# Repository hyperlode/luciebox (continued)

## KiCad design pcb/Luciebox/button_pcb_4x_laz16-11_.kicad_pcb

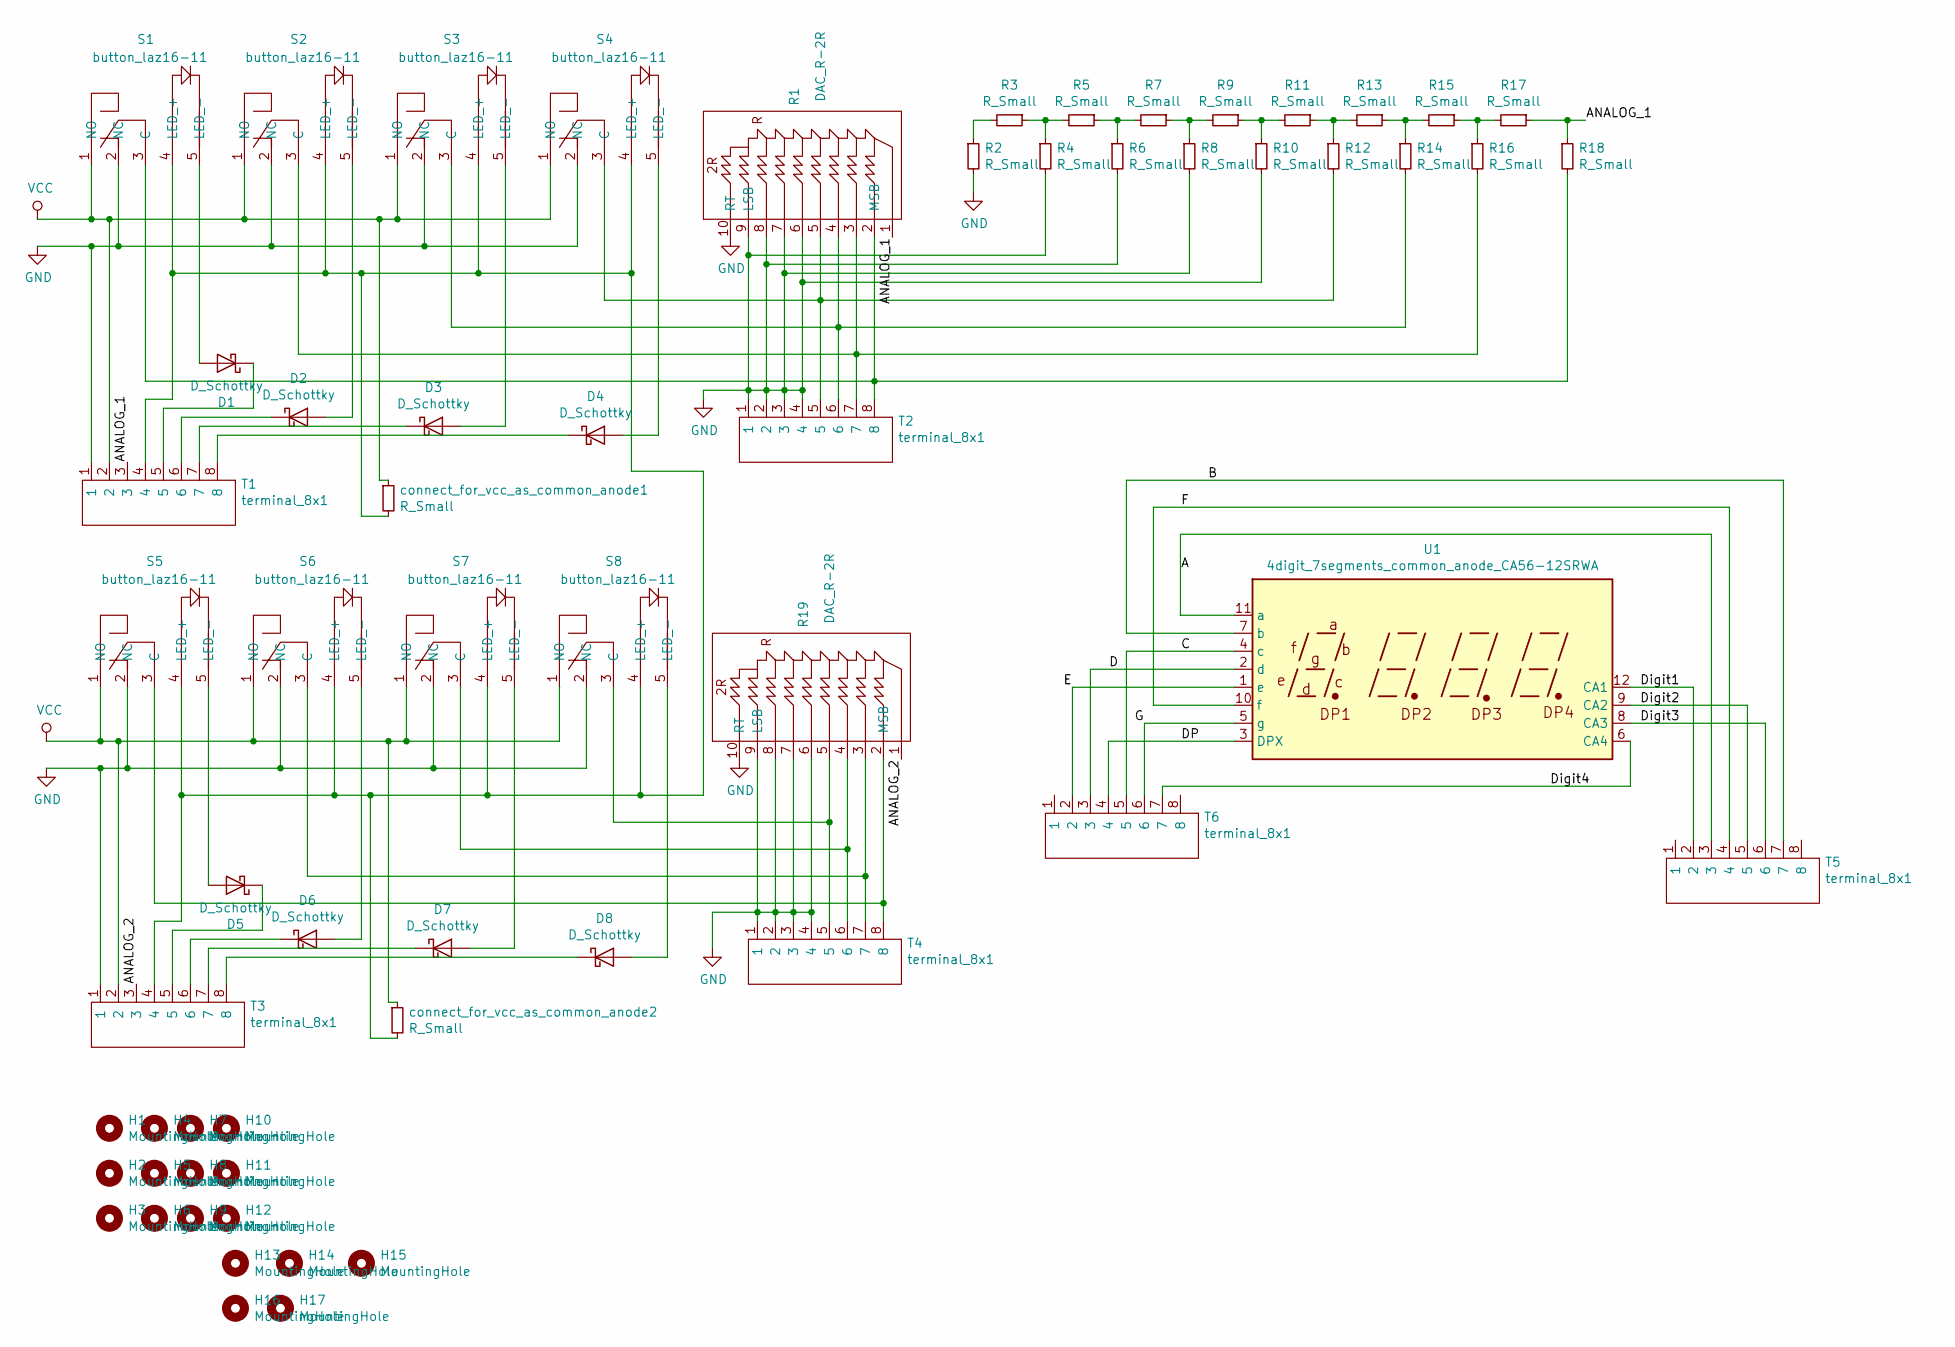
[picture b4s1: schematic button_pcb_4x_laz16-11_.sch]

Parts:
D1, D2, D3, D4, D5, D6, D7, D8: D_Schottky; smd_throughhole_2_pins
H1, H2, H3, H4, H5, H6, H7, H8, H9, H10, H11, H12, H13, H14, H15, H16, H17: MountingHole; MountingHole_4.3mm_M4
R1, R19: DAC_R-2R; SIP-10
R2, R3, R4, R5, R6, R7, R8, R9, R10, R11, R12, R13, R14, R15, R16, R17, R18: R_Small; 1206_0805
S1, S2, S3, S4, S5, S6, S7, S8: button_laz16-11; button_LAZ16-11
T1, T2, T3, T4, T5, T6: terminal_8x1; Terminal_8x1_100mil
U1: 4digit_7segments_common_anode_CA56-12SRWA; CA56-12SRWA
connect_for_vcc_as_common_anode1, connect_for_vcc_as_common_anode2: R_Small; 1206_0805

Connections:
/A: T5.3, U1.11 (a)
/ANALOG_1: R1.1, R17.1, R18.1, T1.3
/ANALOG_2: R19.1, T3.3
/B: T5.7, U1.7 (b)
/C: T6.5, U1.4 (c)
/D: T6.3, U1.2 (d)
/DP: T6.4, U1.3 (DPX)
/Digit1: T5.2, U1.12 (CA1)
/Digit2: T5.5, U1.9 (CA2)
/Digit3: T5.6, U1.8 (CA3)
/Digit4: T6.7, U1.6 (CA4)
/E: T6.2, U1.1 (e)
/F: T5.4, U1.10 (f)
/G: T6.6, U1.5 (g)
GND: R1.6, R1.7, R1.8, R1.9 (LSB), R1.10 (RT), R2.2, R4.2, R6.2, R8.2, R10.2, R19.6, R19.7, R19.8, R19.9 (LSB), R19.10 (RT), S1.2 (NC), S2.2 (NC), S3.2 (NC), S4.2 (NC), S5.2 (NC), S6.2 (NC), S7.2 (NC), S8.2 (NC), T1.1, T2.1, T2.2, T2.3, T2.4, T3.1, T4.1, T4.2, T4.3, T4.4
unnamed: D1.1 (K), T1.5
unnamed: D1.2 (A), S1.5 (LED_-)
unnamed: D2.1 (K), T1.6
unnamed: D2.2 (A), S2.5 (LED_-)
unnamed: D3.1 (K), T1.7
unnamed: D3.2 (A), S3.5 (LED_-)
unnamed: D4.1 (K), T1.8
unnamed: D4.2 (A), S4.5 (LED_-)
unnamed: D5.1 (K), T3.5
unnamed: D5.2 (A), S5.5 (LED_-)
unnamed: D6.1 (K), T3.6
unnamed: D6.2 (A), S6.5 (LED_-)
unnamed: D7.1 (K), T3.7
unnamed: D7.2 (A), S7.5 (LED_-)
unnamed: D8.1 (K), T3.8
unnamed: D8.2 (A), S8.5 (LED_-)
unnamed: R1.2 (MSB), R18.2, S1.3 (C), T2.8
unnamed: R1.3, R16.2, S2.3 (C), T2.7
unnamed: R1.4, R14.2, S3.3 (C), T2.6
unnamed: R1.5, R12.2, S4.3 (C), T2.5
unnamed: R2.1, R3.2
unnamed: R3.1, R4.1, R5.2
unnamed: R5.1, R6.1, R7.2
unnamed: R7.1, R8.1, R9.2
unnamed: R9.1, R10.1, R11.2
unnamed: R11.1, R12.1, R13.2
unnamed: R13.1, R14.1, R15.2
unnamed: R15.1, R16.1, R17.2
unnamed: R19.2 (MSB), S5.3 (C), T4.8
unnamed: R19.3, S6.3 (C), T4.7
unnamed: R19.4, S7.3 (C), T4.6
unnamed: R19.5, S8.3 (C), T4.5
unnamed: S1.4 (LED_+), S2.4 (LED_+), S3.4 (LED_+), S4.4 (LED_+), S5.4 (LED_+), S6.4 (LED_+), S7.4 (LED_+), S8.4 (LED_+), T1.4, T3.4, connect_for_vcc_as_common_anode1.2, connect_for_vcc_as_common_anode2.2
VCC: S1.1 (NO), S2.1 (NO), S3.1 (NO), S4.1 (NO), S5.1 (NO), S6.1 (NO), S7.1 (NO), S8.1 (NO), T1.2, T3.2, connect_for_vcc_as_common_anode1.1, connect_for_vcc_as_common_anode2.1

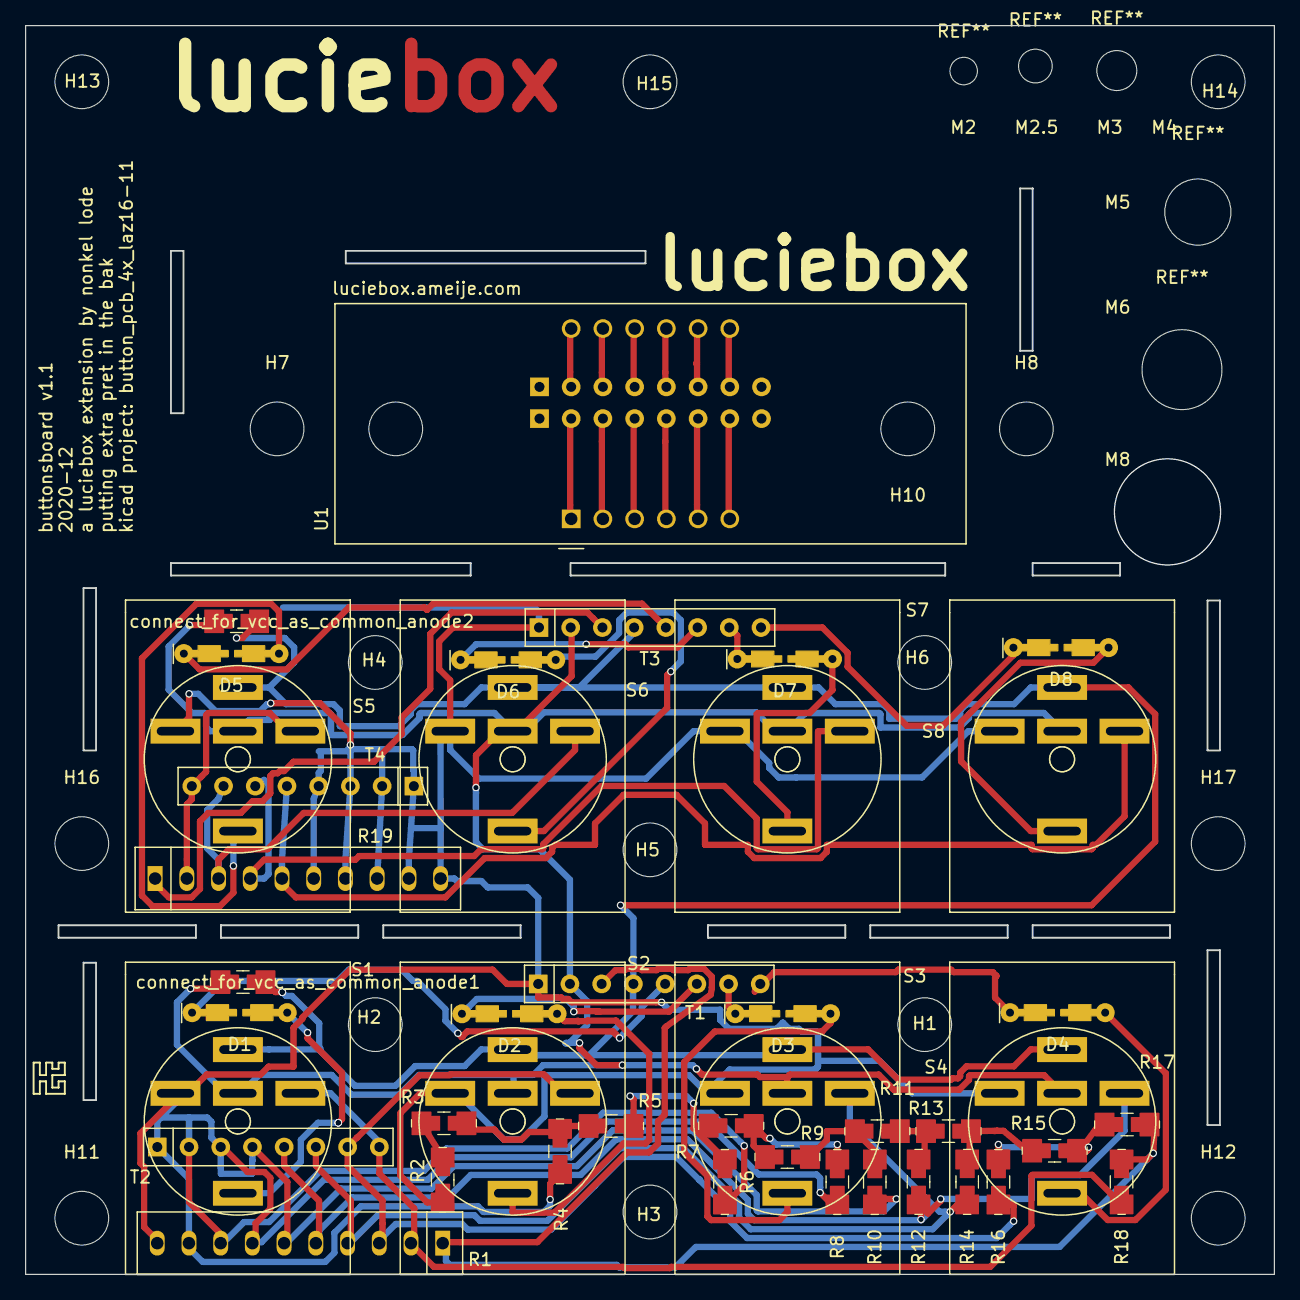
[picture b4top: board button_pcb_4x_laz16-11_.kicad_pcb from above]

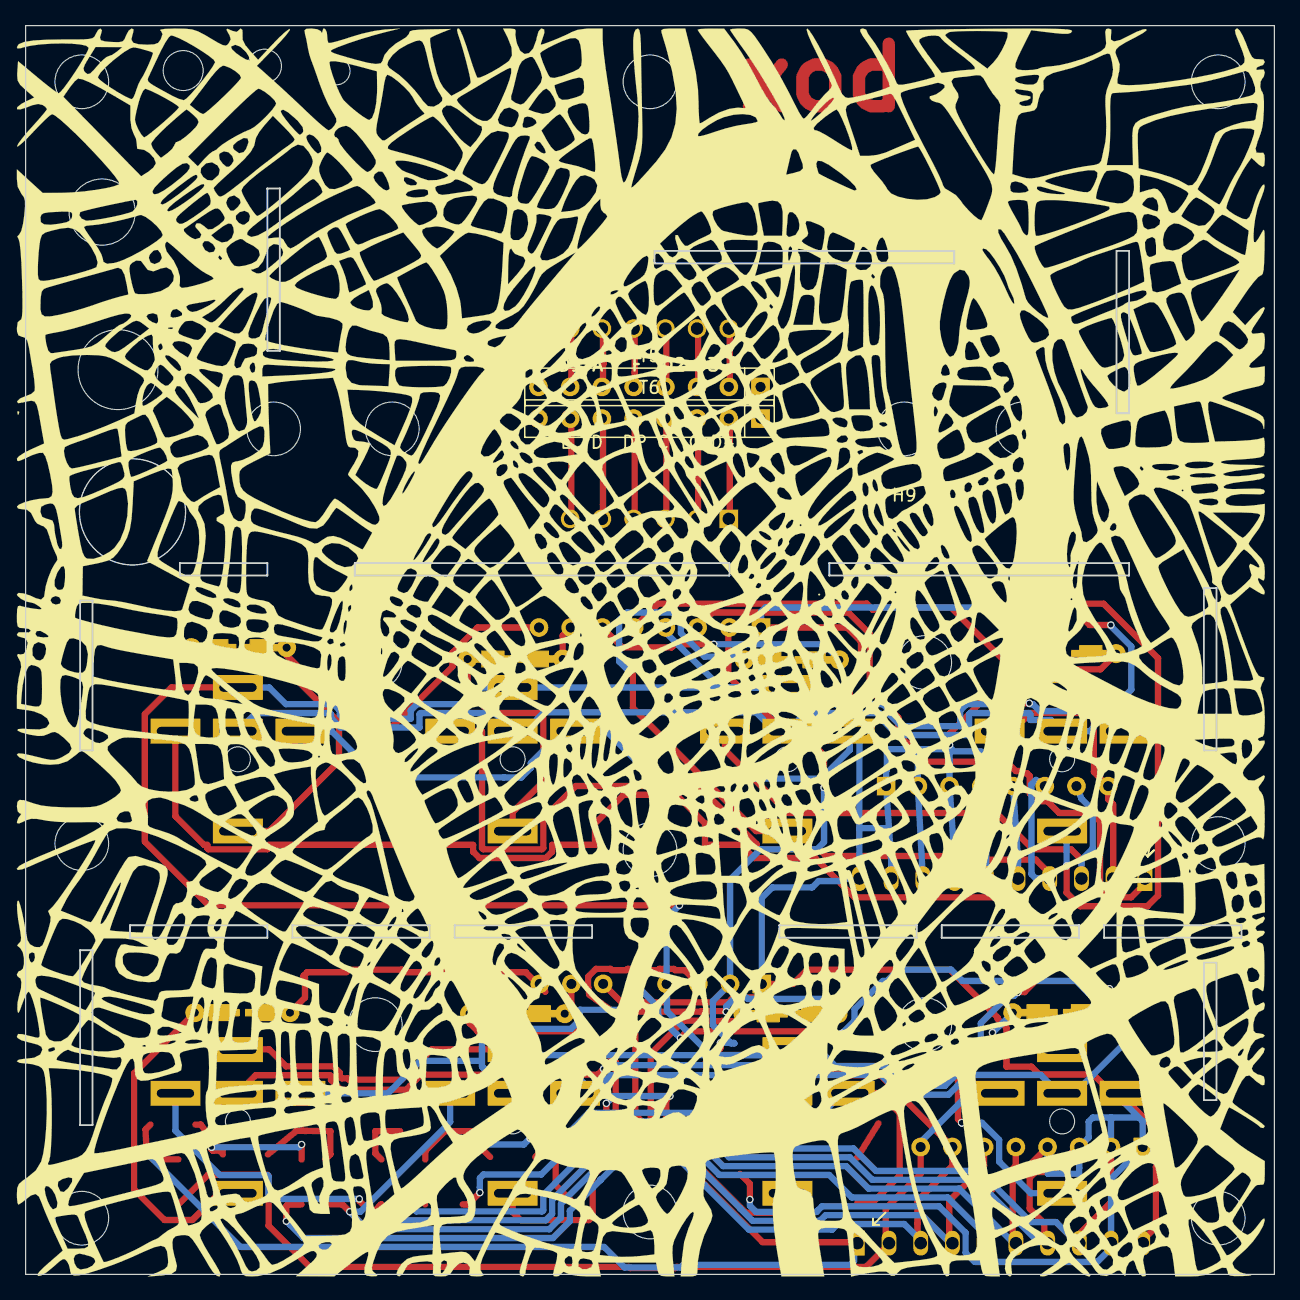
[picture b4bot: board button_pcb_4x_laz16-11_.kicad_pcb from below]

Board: 2 copper layers, 99.9 x 99.9 mm, 61 parts (4 on the bottom side), 49 nets.

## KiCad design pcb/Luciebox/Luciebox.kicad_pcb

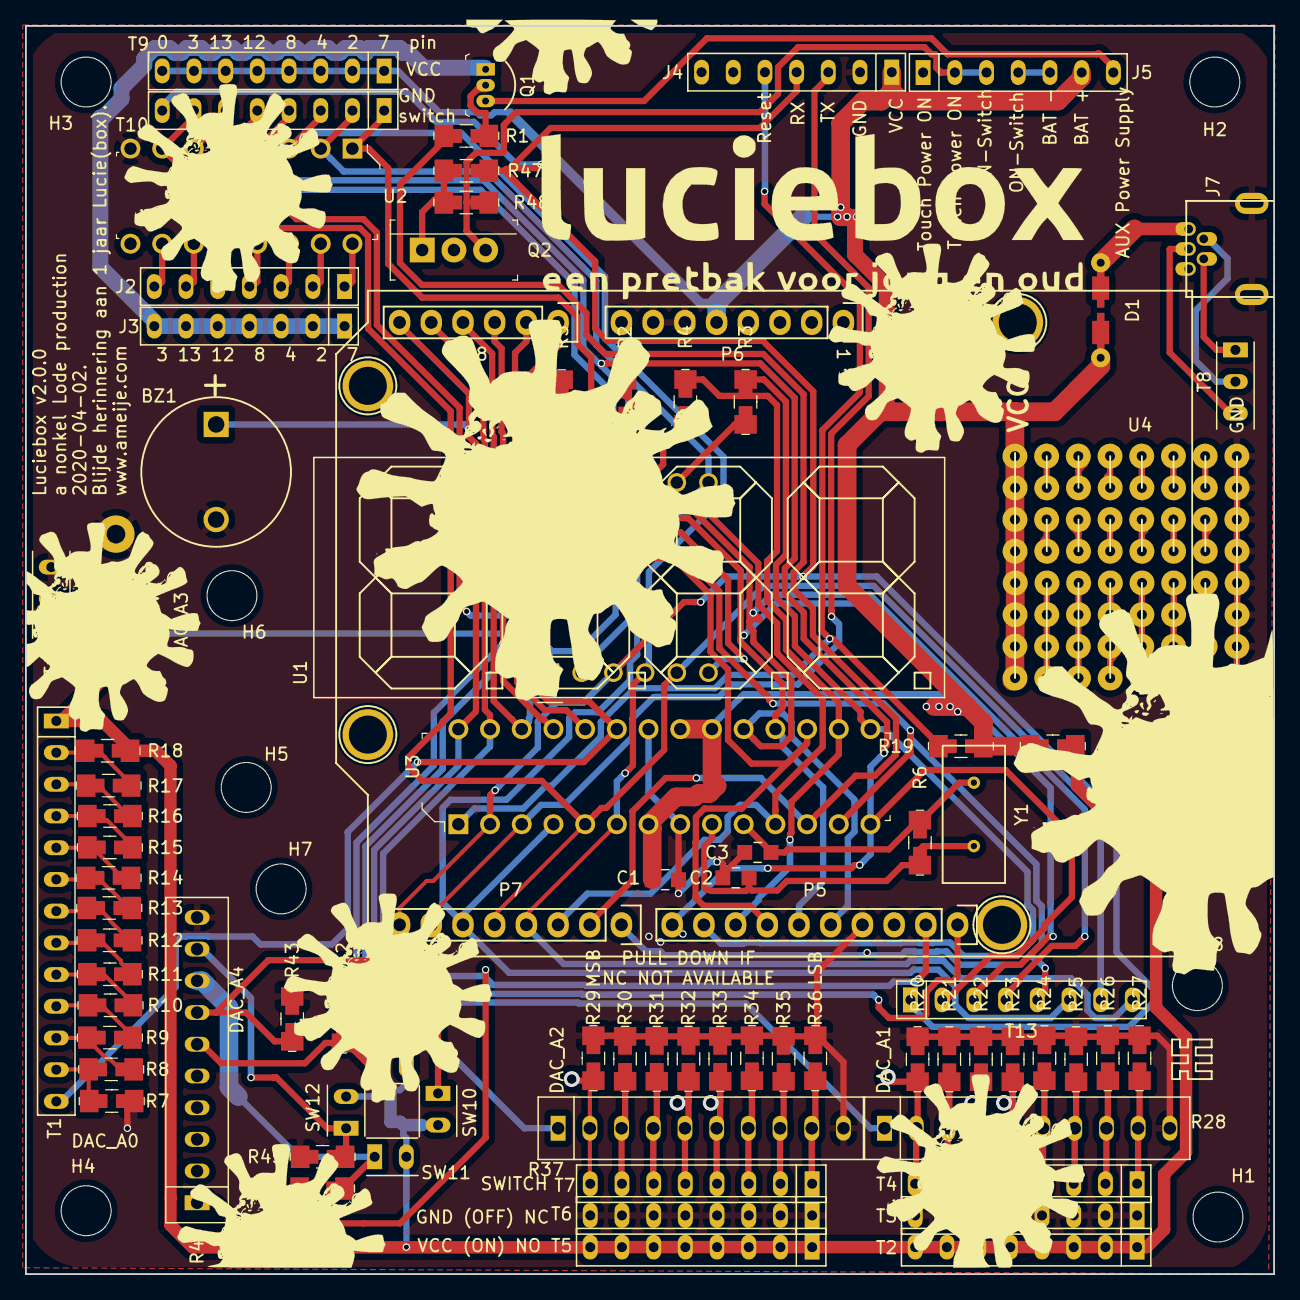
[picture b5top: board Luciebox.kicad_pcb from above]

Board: 2 copper layers, 100.0 x 100.0 mm, 95 parts (0 on the bottom side), 96 nets.

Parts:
BZ1: Buzzer; buzzer
C1: 100nF; 0805
C2, C3: 20pF; 0805
D1: D_Schottky; smd_throughhole_2_pins
H1, H2, H3, H4, H5, H6, H7, H8: MountingHole; MountingHole_4mm
J2, J3, J4, J5: Screw_Terminal_01x07; Terminal_7x1_100mil
J7: USB_B_Mini; usb_mini_Molex-0548190519
P1, P2, P3, P4: CONN_01X01; Arduino_1pin
P5: Digital; Socket_Strip_Arduino_1x10
P6: Power; Socket_Strip_Arduino_1x08
P7: Digital; Socket_Strip_Arduino_1x08
P8: Analog; Socket_Strip_Arduino_1x06
Q1: BC558; TO-92-3
Q2: N-Channel_Mosfet; TO-220-3
R1, R2, R3, R4, R5, R19: 100; 1206_0805
R6: 1M; 1206_0805
R7, R8, R9, R10, R11, R12, R13, R14, R15, R16, R17, R18, R49: 10K; 1206_0805
R20, R21, R22, R23, R24, R25, R26, R27, R29, R30, R31, R32, R33, R34, R35, R36, R42, R43, R44, R45: R_Small; 1206_0805
R28, R37, R46: DAC_R-2R; SIP-10
R47, R48: 100K; 1206_0805
RV1: R_POT; BIG_POTENTIO
SW9, SW10, SW11, SW12: Switch_tilt; Terminal_2x1_100mil
T1: terminal_13x1; Terminal_13x1_100mil
T2, T3, T4, T5, T6, T7, T9, T10, T13: terminal_8x1; Terminal_8x1_100mil
T8, T11: terminal_3x1; Terminal_3x1_100mil
U1: CA56-12SRWA
U2: ULN2003A; DIP-16_W7.62mm
U3: ATmega328-PU; DIP-28_W7.62mm
U4: 8X8PADS; 64_PADS_100mil
Y1: 16MHz; CRYSTAL

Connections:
+12V: J5.7, Q1.3
/0(Rx): J4.4, P7.8, R47.1, T10.8, T13.1, U1.3, U3.2
/1(Tx): J4.3, P7.7, U3.3
/2: P7.6, T10.2, T13.6, U1.7, U2.2, U3.4
/3(PWM): P7.5, T10.7, T13.7, U1.5, U2.7, U3.5
/4: P7.4, T10.3, T13.8, U1.4, U2.3, U3.6
/5(PWM): P7.3, R2.2, U3.11
/6(PWM): P7.2, R1.2, U3.12
/7: P7.1, T10.1, T13.5, U1.11, U2.1, U3.13
/8: P5.10, T10.4, T13.2, U1.2, U2.4, U3.14
/9(PWM): P5.9, R3.2, U3.15
/10(PWM-SS): P5.8, R4.2, U3.16
/11(PWM-MOSI): P5.7, R5.2, U3.17
/12(MISO): P5.6, T10.5, T13.3, U1.1, U2.5, U3.18
/13(SCK): P5.5, T10.6, T13.4, U1.10, U2.6, U3.19
/A0: P8.1, T1.13, U3.23
/A1: P8.2, R28.1, U3.24
/A2: P8.3, R37.1, U3.25
/A3: P8.4, RV1.2, T11.2, U3.26
/A4(SDA): P5.2, P8.5, R46.1, U3.27
/A5(SCL): BZ1.1, P5.1, P8.6, U3.28
GND: BZ1.2, C1.2, C2.1, C3.1, J4.2, J5.1, J7.5, J7.6, P5.4, P6.6, P6.7, Q2.2, R7.2, R20.2, R21.2, R22.2, R23.2, R24.2, R25.2, R26.2, R27.2, R28.10, R29.2, R30.2, R31.2, R32.2, R33.2, R34.2, R35.2, R36.2, R37.10, R42.1, R43.1, R44.1, R45.1, R46.10, RV1.3, T3.1, T3.2, T3.3, T3.4, T3.5, T3.6, T3.7, T3.8, T6.1, T6.2, T6.3, T6.4, T6.5, T6.6, T6.7, T6.8, T11.3, U2.8, U3.8, U3.22, U4.57, U4.58, U4.59, U4.60, U4.61, U4.62, U4.63, U4.64
unnamed: C2.2, R6.1, U3.9, Y1.1
unnamed: C3.2, R6.2, U3.10, Y1.2
unnamed: D1.2, J7.1
unnamed: J2.1, U2.16
unnamed: J2.2, U2.15
unnamed: J2.3, U2.14
unnamed: J2.4, U2.13
unnamed: J2.5, U2.12
unnamed: J2.6, U2.11
unnamed: J2.7, U2.10
unnamed: J3.1, J3.2, J3.3, J3.4, J3.5, J3.6, J3.7, Q1.1
unnamed: J4.5, R19.2, U3.1
unnamed: J5.2, J5.3, Q2.3, R48.2
unnamed: J5.4, J5.5
unnamed: J7.2, T8.2
unnamed: J7.3, T8.3
unnamed: J7.4, T8.1
unnamed: Q1.2, R1.1
unnamed: Q2.1, R47.2, R48.1
unnamed: R2.1, U1.6
unnamed: R3.1, U1.8
unnamed: R4.1, U1.9
unnamed: R5.1, U1.12
unnamed: R7.1, R8.2, T1.12
unnamed: R8.1, R9.2, T1.11
unnamed: R10.1, R11.2, T1.9
unnamed: R9.1, R10.2, T1.10
unnamed: R11.1, R12.2, T1.8
unnamed: R12.1, R13.2, T1.7
unnamed: R13.1, R14.2, T1.6
unnamed: R14.1, R15.2, T1.5
unnamed: R15.1, R16.2, T1.4
unnamed: R16.1, R17.2, T1.3
unnamed: R17.1, R18.2, T1.2
unnamed: R20.1, R28.2, T4.8
unnamed: R21.1, R28.3, T4.7
unnamed: R22.1, R28.4, T4.6
unnamed: R23.1, R28.5, T4.5
unnamed: R24.1, R28.6, T4.4
unnamed: R25.1, R28.7, T4.3
unnamed: R26.1, R28.8, T4.2
unnamed: R27.1, R28.9, T4.1
unnamed: R29.1, R37.2, T7.8
unnamed: R30.1, R37.3, T7.7
unnamed: R31.1, R37.4, T7.6
unnamed: R32.1, R37.5, T7.5
unnamed: R33.1, R37.6, T7.4
unnamed: R34.1, R37.7, T7.3
unnamed: R35.1, R37.8, T7.2
unnamed: R36.1, R37.9, T7.1
unnamed: R42.2, R46.6, SW9.1
unnamed: R43.2, R46.7, SW10.1
unnamed: R44.2, R46.8, SW11.1
unnamed: R45.2, R46.9, SW12.1
unnamed: U4.9, U4.10, U4.11, U4.12
unnamed: U4.13, U4.14
unnamed: U4.15, U4.16
unnamed: U4.17, U4.18, U4.19, U4.20
unnamed: U4.21, U4.22
unnamed: U4.23, U4.24
unnamed: U4.25, U4.26, U4.27, U4.28
unnamed: U4.29, U4.30
unnamed: U4.31, U4.32
unnamed: U4.33, U4.34, U4.35, U4.36
unnamed: U4.37, U4.38
unnamed: U4.39, U4.40
unnamed: U4.41, U4.42, U4.43, U4.44
unnamed: U4.45, U4.46
unnamed: U4.47, U4.48
unnamed: U4.49, U4.50, U4.51, U4.52
unnamed: U4.53, U4.54
unnamed: U4.55, U4.56
VCC: C1.1, D1.1, J4.1, J5.6, P6.5, R19.1, R49.1, T9.1, T9.2, T9.3, T9.4, T9.5, T9.6, T9.7, T9.8, U3.7, U3.20, U3.21, U4.1, U4.2, U4.3, U4.4, U4.5, U4.6, U4.7, U4.8
VCC_minimalCurrent: R18.1, R49.2, RV1.1, SW9.2, SW10.2, SW11.2, SW12.2, T1.1, T2.1, T2.2, T2.3, T2.4, T2.5, T2.6, T2.7, T2.8, T5.1, T5.2, T5.3, T5.4, T5.5, T5.6, T5.7, T5.8, T11.1

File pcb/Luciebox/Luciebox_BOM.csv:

Reference, Value, Footprint, Datasheet
"P6","Power","Socket_Arduino_Uno:Socket_Strip_Arduino_1x08",""
"P8","Analog","Socket_Arduino_Uno:Socket_Strip_Arduino_1x06",""
"P1","CONN_01X01","Socket_Arduino_Uno:Arduino_1pin",""
"P2","CONN_01X01","Socket_Arduino_Uno:Arduino_1pin",""
"P3","CONN_01X01","Socket_Arduino_Uno:Arduino_1pin",""
"P4","CONN_01X01","Socket_Arduino_Uno:Arduino_1pin",""
"P7","Digital","Socket_Arduino_Uno:Socket_Strip_Arduino_1x08",""
"P5","Digital","Socket_Arduino_Uno:Socket_Strip_Arduino_1x10",""
"U1","CA56-12SRWA","Luciebox:CA56-12SRWA","http://www.kingbrightusa.com/images/catalog/SPEC/CA56-12SRWA.pdf"
"R3","100","Luciebox:1206_0805","~"
"R4","100","Luciebox:1206_0805","~"
"R5","100","Luciebox:1206_0805","~"
"U2","ULN2003A","Luciebox:DIP-16_W7.62mm","http://www.ti.com/lit/ds/symlink/uln2003a.pdf"
"R2","100","Luciebox:1206_0805","~"
"R1","100","Luciebox:1206_0805","~"
"Q1","BC558","Luciebox:TO-92-3","http://www.fairchildsemi.com/ds/BC/BC557.pdf"
"J2","Screw_Terminal_01x07","Luciebox:Terminal_7x1_100mil","~"
"J3","Screw_Terminal_01x07","Luciebox:Terminal_7x1_100mil","~"
"U3","ATmega328-PU","Luciebox:DIP-28_W7.62mm","http://ww1.microchip.com/downloads/en/DeviceDoc/ATmega328_P%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"
"R7","10K","Luciebox:1206_0805","~"
"R8","10K","Luciebox:1206_0805","~"
"R9","10K","Luciebox:1206_0805","~"
"R10","10K","Luciebox:1206_0805","~"
"R11","10K","Luciebox:1206_0805","~"
"R12","10K","Luciebox:1206_0805","~"
"R13","10K","Luciebox:1206_0805","~"
"R14","10K","Luciebox:1206_0805","~"
"R15","10K","Luciebox:1206_0805","~"
"R16","10K","Luciebox:1206_0805","~"
"R17","10K","Luciebox:1206_0805","~"
"R18","10K","Luciebox:1206_0805","~"
"T1","terminal_13x1","Luciebox:Terminal_13x1_100mil",""
"RV1","R_POT","Luciebox:BIG_POTENTIO","~"
"BZ1","Buzzer","Luciebox:buzzer","~"
"Y1","16MHz","Luciebox:CRYSTAL","~"
"R6","1M","Luciebox:1206_0805","~"
"C2","20pF","Luciebox:0805","~"
"C3","20pF","Luciebox:0805","~"
"C1","100nF","Luciebox:0805","~"
"R19","100","Luciebox:1206_0805","~"
"J4","Screw_Terminal_01x07","Luciebox:Terminal_7x1_100mil","~"
"Q2","N-Channel_Mosfet","Luciebox:TO-220-3","https://www.onsemi.com/pub/Collateral/FQP30N06L-D.pdf"
"R47","100K","Luciebox:1206_0805","~"
"R48","100K","Luciebox:1206_0805","~"
"J5","Screw_Terminal_01x07","Luciebox:Terminal_7x1_100mil","~"
"T11","terminal_3x1","Luciebox:Terminal_3x1_100mil",""
"H4","MountingHole","MountingHole:MountingHole_4mm","~"
"H1","MountingHole","MountingHole:MountingHole_4mm","~"
"H2","MountingHole","MountingHole:MountingHole_4mm","~"
"H3","MountingHole","MountingHole:MountingHole_4mm","~"
"H8","MountingHole","MountingHole:MountingHole_4mm","~"
"H7","MountingHole","MountingHole:MountingHole_4mm","~"
"H6","MountingHole","MountingHole:MountingHole_4mm","~"
"H5","MountingHole","MountingHole:MountingHole_4mm","~"
"U4","8X8PADS","Luciebox:64_PADS_100mil",""
"R49","10K","Luciebox:1206_0805","~"
"J7","USB_B_Mini","Luciebox:usb_mini_Molex-0548190519","~"
"D1","D_Schottky","Luciebox:smd_throughhole_2_pins","~"
"T8","terminal_3x1","Luciebox:Terminal_3x1_100mil",""
"T10","terminal_8x1","Luciebox:Terminal_8x1_100mil",""
"T9","terminal_8x1","Luciebox:Terminal_8x1_100mil",""
"T13","terminal_8x1","Luciebox:Terminal_8x1_100mil",""
"R27","R_Small","Luciebox:1206_0805","~"
"R26","R_Small","Luciebox:1206_0805","~"
"R25","R_Small","Luciebox:1206_0805","~"
"R24","R_Small","Luciebox:1206_0805","~"
"R23","R_Small","Luciebox:1206_0805","~"
"R22","R_Small","Luciebox:1206_0805","~"
"R21","R_Small","Luciebox:1206_0805","~"
"R20","R_Small","Luciebox:1206_0805","~"
"R28","DAC_R-2R","Luciebox:SIP-10","https://www.bourns.com/docs/Product-Datasheets/R2R.pdf"
"T4","terminal_8x1","Luciebox:Terminal_8x1_100mil",""
"T3","terminal_8x1","Luciebox:Terminal_8x1_100mil",""
"T2","terminal_8x1","Luciebox:Terminal_8x1_100mil",""
"R36","R_Small","Luciebox:1206_0805","~"
"R35","R_Small","Luciebox:1206_0805","~"
"R34","R_Small","Luciebox:1206_0805","~"
"R33","R_Small","Luciebox:1206_0805","~"
"R32","R_Small","Luciebox:1206_0805","~"
"R31","R_Small","Luciebox:1206_0805","~"
"R30","R_Small","Luciebox:1206_0805","~"
"R29","R_Small","Luciebox:1206_0805","~"
"R37","DAC_R-2R","Luciebox:SIP-10","https://www.bourns.com/docs/Product-Datasheets/R2R.pdf"
"T7","terminal_8x1","Luciebox:Terminal_8x1_100mil",""
"T6","terminal_8x1","Luciebox:Terminal_8x1_100mil",""
"T5","terminal_8x1","Luciebox:Terminal_8x1_100mil",""
"R44","R_Small","Luciebox:1206_0805","~"
"R43","R_Small","Luciebox:1206_0805","~"
"R46","DAC_R-2R","Luciebox:SIP-10","https://www.bourns.com/docs/Product-Datasheets/R2R.pdf"
"SW9","Switch_tilt","Luciebox:Terminal_2x1_100mil",""
"SW10","Switch_tilt","Luciebox:Terminal_2x1_100mil",""
"SW11","Switch_tilt","Luciebox:Terminal_2x1_100mil",""
"SW12","Switch_tilt","Luciebox:Terminal_2x1_100mil",""
"R45","R_Small","Luciebox:1206_0805","~"
"R42","R_Small","Luciebox:1206_0805","~"

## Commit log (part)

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2020-02-19 update Simon Says
2020-02-19 update numbers and letters. no big latch needed
2020-02-20 simon working nicely, prepare for multi player
2020-02-21 simon multiplayer mode working
2020-02-21 before simon refactor with players array (set 4 bytes array to 8 bytes. affects reaction game and displayfun mode
2020-02-21 simon custom game
2020-02-22 reorganize apps structure
2020-02-23 various changes and little bugfixes
2020-02-23 pomodoro app: multitimer time select
2020-02-23 pomodoro performance tracking 2 registers good and bad work. Press the button according to your behaviour. Still need to implement a random beep to remind you to press at that moment.
2020-02-23 pomodoro finishing up (fingers crossed)
2020-02-23 rework app selector function. I just learned that switch statements take a lot of memory. 500 bytes extra for adding some more options? yoink! I will try with function pointers. Or i'll have to rewin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
2020-02-27 reworking draw app, make things A LOT less complicated
2020-02-29 draw load drawings from eeprom
2020-03-03 draw app: insert drawing, delete drawing with shifting everything. This way frames can be edited to fit into a movie. NICE!
2020-03-04 untested commit, before taking segment manipulation out of draw function (for the hack mode, which has a very similar way of functioning)
2020-03-04 draw mode working with detangling.
2020-03-05 draw game (copy a given image ) prototype ready and playable
2020-03-05 Neat up code. Formatting function ALT+SHIFT+F discovered in visual studio code
2020-03-06 drawGame bugfix
2020-03-06 refactoring Display management. Almost compiling...
2020-03-06 display refactor. Test multiplexer
2020-03-06 display refactor : buttons led lights working
2020-03-06 display refactor: chars working
2020-03-07 progressive change towards v2.0
2020-03-07 rework display: multitimer, sequencer, reaction game: done
2020-03-08 rework song player (work in progress)
2020-03-09 Busy reworking modeSoundNotes.
2020-03-11 modify pcb v2.0. nearly finished. Choose box.
2020-03-12 draw game basic version finished. numbers, letter, random, clock reading
2020-03-13 quick commit while changing to platformio at work
2020-03-13 hacktime app in progress
2020-03-13 increase decrease at potentio optimize
2020-03-14 bad bad pointer bugfix
2020-03-15 rework metronome. Not the memory gain I thought I was going to see...
2020-03-16 hacktime display memory in different formats.
2020-03-17 hacktime making progress. Running through memory works fine. Prepare for change byte.
2020-03-18 compress momentary 2 and 3 -- and ++ values
2020-03-20 compress and bugfix
2020-03-22 compress
2020-03-22 make more sense of standard texts. No more sillyness there!
2020-03-23 change pretbaksettings threshold values buttons. analog input misery
2020-03-23 compress settings menu
2020-03-28 pcb change extra header so holes line up for lights to buttons.
2020-04-04 change pictograms
2020-04-08 modeSoundNotes work on scales.Todo going down, change key
2020-04-10 mode sound note basic finished
2020-04-10 Generalize progmem to display to optimize memory
2020-04-11 Bugfix in sound note scales
2020-04-12 Generalize sound scale before changing User Interface
2020-04-12 Finetune the sound notes appliation user experience.
2020-04-14 Optimize memory for button presses. Still room for improvement
2020-08-16 undo prototype display exception
2020-09-03 Set multiplexer I/O to high impedance to 5V button lights wto work. Tested on adapted prototype.
2020-09-05 I must have coincidentally auto formatted apps.cpp
2020-09-06 fix bug: wrong find and replace instances of big_latching were changed by extra_latching
2020-09-06 attempt to optimize. failed.
2020-09-09 fix bug in hex hero.
2020-09-12 work on reaction app. memory condensing. icon pictures
2020-09-12 reaction game eeprom update for high scores . reset is needed as eeprom layout changed.
2020-10-11 rotary encoder demo
2020-10-12 change apps to accomodate for encoder. untested. disable reaction app. 0.5% over mem :(
2020-10-16 implement more changes to accomodate for encoder_dial
2020-10-17 repair sequencer (serial enabled, multitimer disabled)
2020-10-18 repair draw app
2020-10-21 all apps ON. juuuussst 100% memory. G segment not working. hardware?
2020-10-22 bugfix metronome speed change only when ticking
2020-10-22 simon finished
2020-10-26 dial implementation for sequencer
2020-10-28 erase display at start of every cycle
2020-10-28 double stopwatch. Two songs ditched to get it on there....
2020-10-29 minor updates on tilt and some general niceness
2020-10-29 Pomodoro bugfix
2020-11-02 movie player rework. Saves like 0.3% flash after quite some work. Totally worth it!
2020-11-04 finished base animation movie player
2020-11-05 compress memory
2020-11-05 clean up buzzer
2020-11-05 rework buzzer songs --> almost done but strange error with songindex
2020-11-06 clean up apps.h file
2020-11-07 update and finish music player and movie player . All apps up and running, memory nice and full
2020-11-07 optimize drawing controls got me one percent of memory baby!
2020-11-07 create new feature : screen save app
2020-11-07 improve metronome
2020-11-08 memory optimization with timer init
2020-11-09 change screensave to dreamtime name
2020-11-09 tally keeper edit/view with latching
2020-11-09 tally keeper add functionality button to apply delta to all counters if requested
2020-11-09 small memory optimizations
2020-12-04 pcb new version v3 . Chaotic history
2020-12-07 pcb work on button pcb
2020-12-10 before finishing v3
2020-12-12 published and ordered v3 luciebox v1 buttonboard. Gerbers included
2020-12-14 all button lights working
2020-12-15 default light on per button press (not all apps loaded)
2020-12-15 lights metronome flash
2020-12-16 draw app lights. memory 2 bytes too small.
2020-12-16 bugfix latching button extra was not indicated as indexed.
2020-12-16 minimultitimer lights ok. Prepare to get rid of class to save memory
2020-12-17 optimize multitimer integration
2020-12-23 v3_pcb firmware adjustment
2020-12-24 mute mode in sound, simon says lights bug fix. Mem full
2020-12-26 multitimer app improvements Free the shift app selector button in multitimer. But, no app to add to the free spot.
2020-12-27 multitimer app uptimized and cleaned out
2020-12-27 add quizmaster back to the apps. No more tilt switches. The slot is free, the memory is not...
2020-12-28 button and lights app change to settings name. Draw app
2021-03-11 SET to debug mode, but multitimer crash issue solved
2021-03-12 v3 corona differentiate with v2 for neater cables.
2021-03-13 reaction game countdown mode fixed
2021-03-14 Sequencer auto generate song at load time
2021-03-16 attempt to optimize song memory footprint is too futile to press through
2021-03-16 eeprom update instead of write. + multitimer instant start
2021-03-16 improve settings menu, eeprom behaviour (partial reset), set power cycler counter
2021-03-17 improve quizmaster app, it now accurately detects first button press. And no more simultaneous ones.
2021-03-18 clean the .ino file. Cosmetically
2021-03-18 update settings mode to properly display settings
2021-03-18 pomodoro timer settings to eeprom
2021-03-19 draw insert and delete pictures bugfix
2021-03-21 small changes and layout
2021-04-07 metronome, save some bytes
2021-04-08 enhance simon app
2021-04-08 enable_eeprom tag updated to work well
2021-04-08 rearrange apps.h
2021-04-08 Quizmaster score assignment with dial
2021-04-09 inactivity timer up and running
2021-04-09 optimize weighted random
2021-04-11 rework hack mode
2021-04-13 add whack a bird init lights. Still a bit too big too compile. make -500 default for timers.
2021-04-13 fix buzzer note display bug
2021-04-17 visual screen fill like hourglass for pomodoro timer. Size exploded though. Check it out!
2021-04-18 pomodoro changing to hourglass. Still to big. in the middle of making i smaller
2021-04-20 fit it all into the memory
2021-04-21 bugfix eeprom range games --> pointer casting was wrong
2021-04-21 documentation luciebox drawing
2021-04-21 repo clean up
2021-04-21 F303. settings mode change easier debug. small bugfixes
2021-09-15 rework dreammode to baby activity center
2021-09-30 add Battery level meter, but not activated because of memory
2021-09-30 add optimization to buzzer, set notes count as define
2021-10-01 rework buzzer buffer treatement
2021-10-01 add battery voltage level menu item in settings menu
2021-10-03 bugfix buzzer notes
2021-10-05 sequencer program rework
2021-10-15 erase non used code
2021-11-24 Restore pcb components
2022-01-12 ignore kicad pcb backup folder
2022-01-12 apps.cpp layout standardized
2022-01-12 set inactivity timeout to one hour
2022-01-13 add separate splash screen per app for non selector button version
2022-01-16 auto power off working. Disabled Simon - App
2022-01-26 Create software simulated latching buttons with momentary buttons. Works on settings app already.
2022-01-27 busy transforming apps to use Software latching button instead of physical ones
2022-01-30 fix drawing game app and app selector button bug
2022-01-30 fine tune auto power off, shut down
2022-01-31 convert reaction app to work well with momentary buttons
2022-02-20 Improve Pomodoro timer for non selector version
2022-02-22 Auto formatting with ALT+SHIFT+F in vscode
2022-02-22 Let app navigation lights blink in app selection mode
2022-05-16 Pcb v4 setup with kicad6. Button board --> before erasing smd components from the board
2022-06-01 layout main board start
2022-11-08 Progress on pcb's
2022-11-09 Moved boards connector. Main board ready for traces.
2022-11-09 Add artwork. Copy screenshot to gimp to delete parts you don't want with silkscreen from original image. Than, generate new artwork. from burst, set to 150mm export
2022-11-14 PCB v4 sent for production
2022-12-09 Main pcb v4 values
2023-03-07 Pcb V5
2023-03-07 Fix splash screen button light snake
2023-03-09 Make dial more sensitive in apps
2023-03-09 Rework Multitimer. Make room for survive timeout function. Not yet implemented
2023-03-10 Bugfix: stopwatch laptime enable
2023-03-10 Add sound to chrono
2023-12-31 Whackamole thinking and deciding to not let the lights briefly go out if twice the same position is chosen in sequence
2024-01-02 Buffix, whackabird highscore ruins sound sequence because victory song used same buffer
2024-01-03 Layout and cleanup
2024-01-06 Multitimer optimizations. Single player. Display
2024-01-06 Multitimer no minute beeps if only one timer
2024-01-07 Layouting
2024-01-08 Optimize memory for blinking button lights
2024-01-08 Memory optimization multitimer with lights. Not working yet
2024-01-08 Multitimer memory saving.
2024-01-12 Game works well, but max size exceeded by 10 bytes...
2024-01-14 Stopwatch, prevent autopower off
2024-01-15 Free up memory by combining momentary button press positive edge index
2024-01-15 Inactivity timer test
2024-01-16 Simon app, never let the same player start at the beginning of a round (playing feedback)
2024-01-16 Simon, increase players to 99. Player display improve
2024-01-18 Bugfig Simon single player random choser infinit while looop
2024-01-19 Simon rework. all good. But, for custom build up, should be lighting up long after player choses, not new level...
2024-01-22 Simon says, improve custom player behaviour. Not ok yet.
2024-01-26 Generalize Buzzer done playing function, too big size
2024-01-26 Simon memory optimize
2024-01-28 Change momentary and latching buttons to big and small buttons. Change documentation drawings
2024-01-29 Simon custom adding change end level. not compiling
2024-01-30 Found some memory in tallykeeper. Compiles. On airplane, not tested
2024-02-02 Tally rework. In middle of it
2024-02-03 Tally keeper update. After five years, a breakthrough. We can handle negative numbers
2024-02-03 Store tally keeper values in eeprom. Works. Can't compile with all apps enabled . too big
2024-02-03 Update tally for style. 0 bytes left
2024-02-03 Buzzer rest rework, not yet compiling
2024-02-06 Free up memory by transitioning 16 to 8 bits. Tally keeping app improved
